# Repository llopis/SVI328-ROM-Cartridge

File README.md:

# SVI328-ROM-Cartridge
Generic 32KB ROM cartridge for the Spectravideo 328.

Motivated by the SVI328-to-MSX cartridge, but it should work for any cartridge ROM.
https://youtu.be/hb8DHYpg0qM

Case 3D model modified by mrbyte from https://hobbyretro.com/

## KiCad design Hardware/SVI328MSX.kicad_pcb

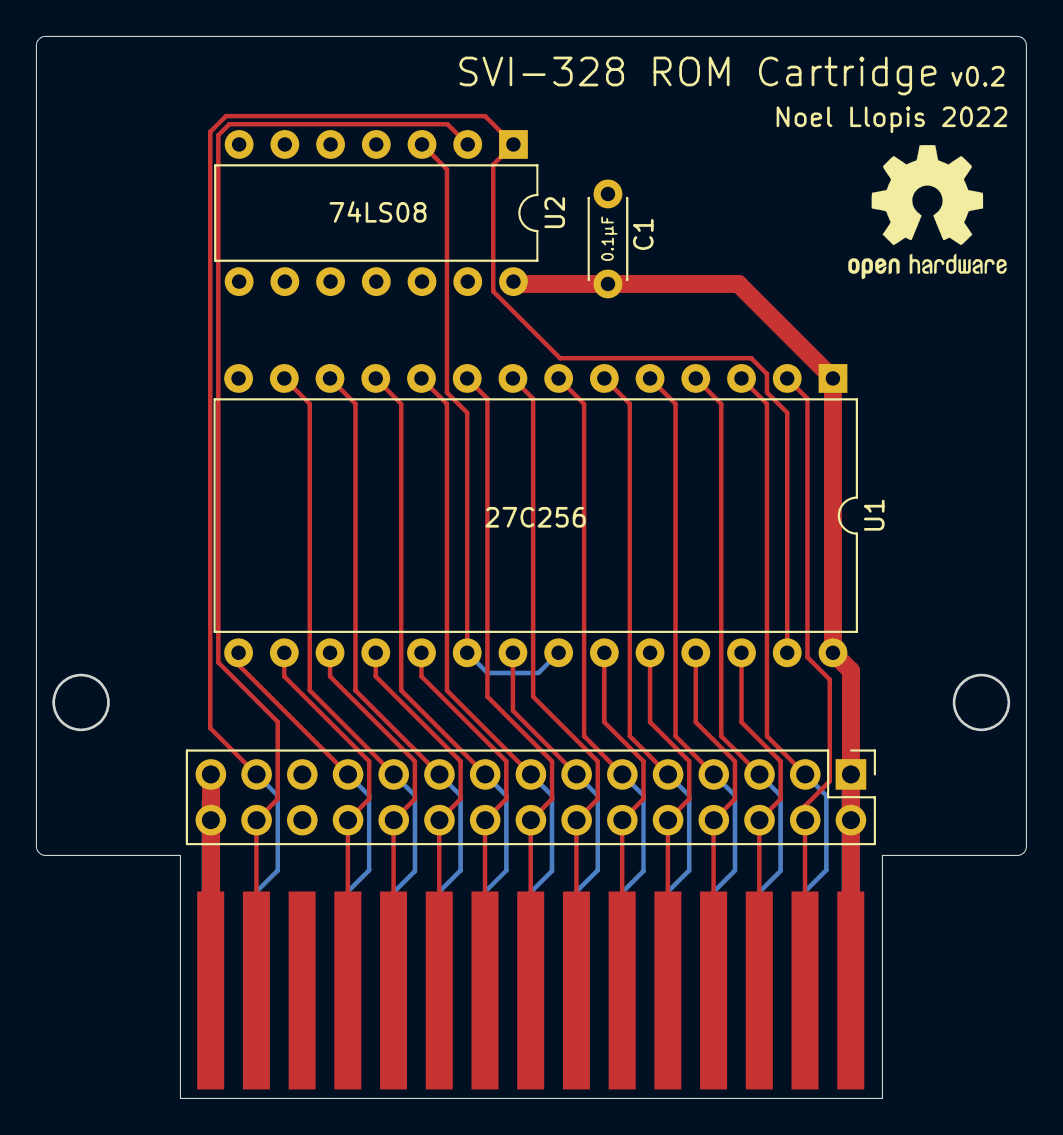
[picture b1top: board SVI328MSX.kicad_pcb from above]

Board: 2 copper layers, 55.0 x 59.0 mm, 5 parts (0 on the bottom side), 27 nets.

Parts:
C1: 0.1µF; C_Disc_D4.3mm_W1.9mm_P5.00mm
J1: Conn_02x15_Odd_Even; svi328_cartridge
J2: Conn_02x15_Odd_Even; PinHeader_2x15_P2.54mm_Vertical
U1: 27C256; DIP-28_W15.24mm
U2: 74LS08; DIP-14_W7.62mm

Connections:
A0: J1.15, J2.15, U1.10
A1: J1.16, J2.16, U1.9
A2: J1.14, J2.14, U1.8
A3: J1.11, J2.11, U1.7
A4: J1.9, J2.9, U1.6
A5: J1.7, J2.7, U1.5
A6: J1.5, J2.5, U1.4
A7: J1.3, J2.3, U1.3
A8: J1.8, J2.8, U1.25
A9: J1.10, J2.10, U1.24
A10: J1.13, J2.13, U1.21
A11: J1.12, J2.12, U1.23
A12: J1.4, J2.4, U1.2
A13: J1.6, J2.6, U1.26
CS1: J1.27, J2.27, U1.27, U2.1
CS2: J1.28, J2.28, U2.2
D0: J1.17, J2.17, U1.11
D1: J1.19, J2.19, U1.12
D2: J1.21, J2.21, U1.13
D3: J1.23, J2.23, U1.15
D4: J1.24, J2.24, U1.16
D5: J1.22, J2.22, U1.17
D6: J1.20, J2.20, U1.18
D7: J1.18, J2.18, U1.19
GND: C1.2, J1.29, J1.30, J2.29, J2.30, U1.14, U2.4, U2.5, U2.7, U2.9, U2.10, U2.12, U2.13
unnamed: U1.20, U1.22, U2.3
VCC: C1.1, J1.1, J1.2, J2.1, J2.2, U1.1, U1.28, U2.14

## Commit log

2022-07-04 Added Gerber files and renders.
2022-07-06 Removed J1 and J2 labels
2022-07-15 Added video link.
2022-07-15 Case credits
